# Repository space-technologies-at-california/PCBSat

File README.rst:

=============
PCB Satellite
=============
Space Technologies at Cal (https://stac.berkeley.edu)

University of California, Berkeley

Getting Started
===============
Clone this repository. Then:

Eagle
-----
#. Obtain the `STAC Eagle library <https://github.com/space-technologies-at-california/electronics>`_ by running::
   
    git submodule init
    git submodule update

#. `Add the library to Eagle <https://www.instructables.com/id/Adding-a-Library-to-Eagle-CAD/>`_.

Firmware
--------
#. Install `MSP430-GCC <http://www.ti.com/tool/msp430-gcc-opensource>`_ and
   `MSPDebug <https://dlbeer.co.nz/mspdebug/>`_.

#. In *firmware/*, make a new file called *msp430.mk.inc* and specify the path
   to your MSP430-GCC installation. For example::

    MSP430_TOOLCHAIN=/usr/local/gcc-msp430-ti-toolchain-5.01.02.00

#. Run ``make`` from *firmware/* to build all firmware configurations. To
   build a specific configuration, change to the appropriate subdirectory (for
   example, *debug/*) and run ``make``. If ``make`` complains about a missing
   *gitrev.h*, type ``make gitrev.h`` and re-run.

#. To change a build configuration, edit *config.h* in the appropriate
   subdirectory.

Programming
~~~~~~~~~~~
#. Obtain a programmer. We use the MSP430F5529 LaunchPad to program our sprite
   using Spy-Bi-Wire (SBW), but any SBW-compatible programmer should work.

#. Disconnect the 5V, 3V, GND, SBW RST and TST jumpers from the LaunchPad.

#. Connect the 3V, GND, SBW RST and TST jumpers on the ezFET-lite side to the
   target.

#. Run ``make prog`` to program, and run ``make verify`` to read back what was
   programmed.

Simulation
----------
Dependencies: igrf12 (https://github.com/scivision/igrf12)

#. Run ``python3 pull_iss_locdata.py``. This will collect (timestamp, latitude,longitude) data of the ISS for 9 hours at 10 second increments. This will create an output file in the current directory titled ``iss_loc_data_{timestamp}.csv``.  
#. Run ``python3 data_gen.py -f iss_loc_data_{timestamp}.csv`` where timestamp corresponds to the file created in the previous step. This will create an output file in the current directory that contains magnetometer data (x,y,z), gyrometer data (x,y,z), and the expected axis and power that the PCBSat should rotate along in addition to the file's previous contents. This output file will be titled ``full_{timestamp}.csv``. The units for the magnetometer data are Gauss and the units for the gyrometer data are radians/second.  

The models for predicting power and axis are still in progress. 

To run tensorboard, navigate to /simulations/python/ and execute `tensorboard --logdir="tmp/model/"`. Make sure that you have the most recent versions of tensorflow and tensorboard installed. 

Directory Structure
===================
- ./eagle : Contains all necessary Eagle files for the sprite board

  - ./eagle/sprite-test: Contains the version of the sprite manufacture by 
    Bay Area Circuits as a test board. It is largely based on the sprite
    verison created by Zac Manchester here: https://github.com/kicksat/sprite

  - ./eagle/final-sprite: Contains the version of the sprite we are currently
    working on. Our sprite began from the attitude-sprite designed by Zac
    Mancherster here: https://github.com/kicksat/attitude-sprite

  - ./eagle/electronics: STAC Eagle library submodule. See Eagle_. Please add
    any parts to the stac.lbr file contained there.
    
- ./simulation : Contains all the simulation netlists and other data 

- ./firmware : Contains all the firmware for the sprite

- ./gerbers : Contains the gerbers for the sprites. 

`Getting Started with Sprite Development Kit <https://github.com/kicksat/sprite/wiki/Getting-started-with-the-Sprite-Development-Kit>`_

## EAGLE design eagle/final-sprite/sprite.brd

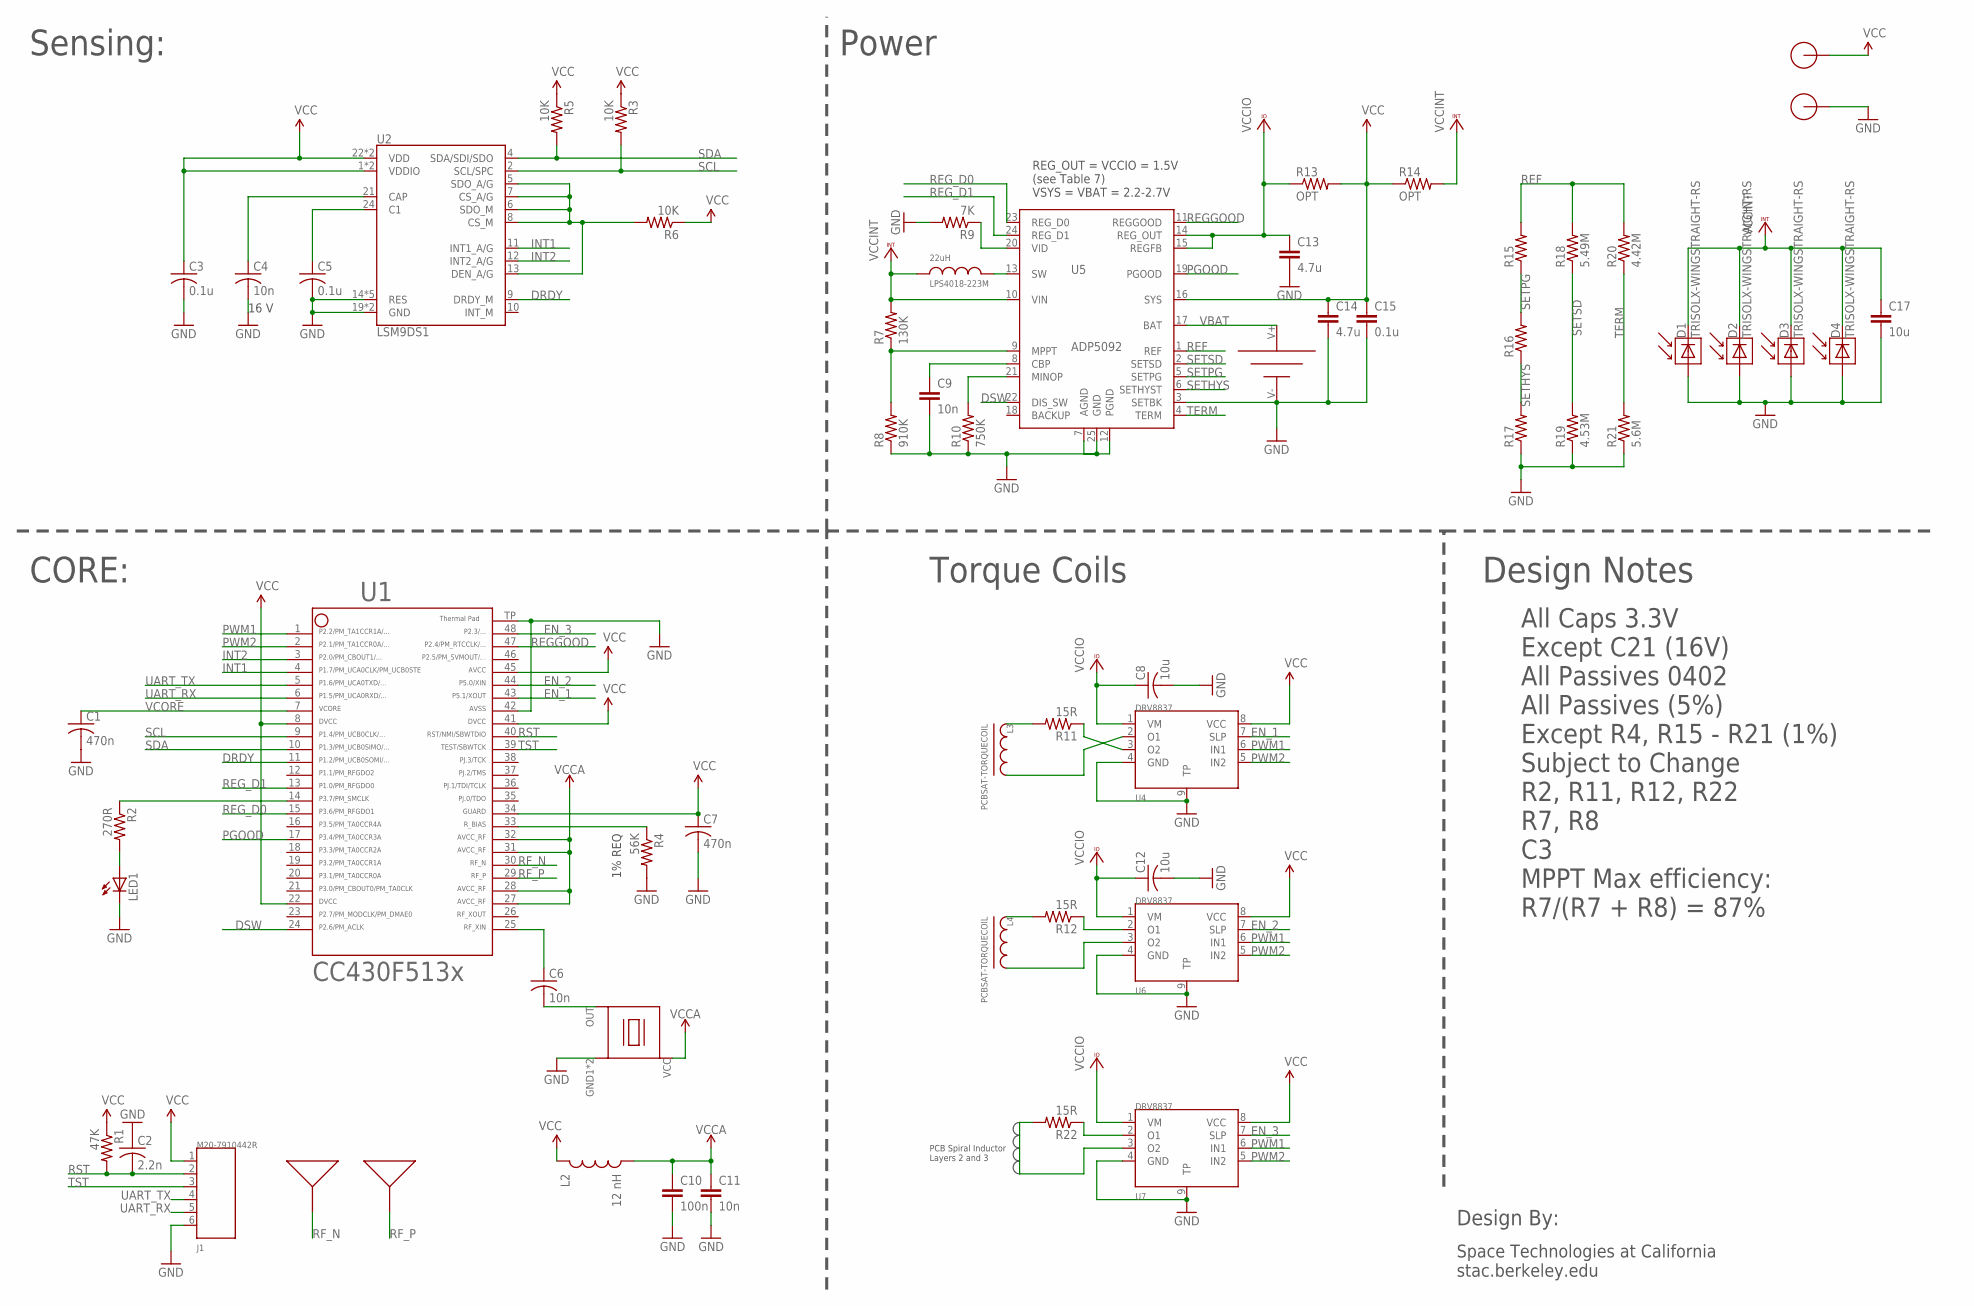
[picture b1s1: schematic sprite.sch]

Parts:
A1, A2: SPRITEANTENNA_ANTENNA
B1: UMAC_UMAC
C1, C7: 470n; C0402
C2: 2.2n; C0402
C3, C5, C15: 0.1u; C0402
C4, C6, C9, C11: 10n; C0402
C8, C12, C17: 10u; C0402
C10: 100n; C0402
C13, C14: 4.7u; C0402
D1, D2, D3, D4: TRISOLX-WINGSTRAIGHT-RS; TRISOLX-STRAIGHT-RS
J1: M20-7910442R
L1: LPS4018-223M
L2: 12 nH; 0603
L3, L4: PCBSAT-TORQUECOIL
LED1: LED0603; LED-0603
R1: 47K; R0402
R2: 270R; R0402
R3, R5, R6: 10K; R0402
R4: 56K; R0402
R7: 130K; R0402
R8: 910K; R0402
R9: 7K; R0402
R10: 750K; R0402
R11, R12, R22: 15R; R0402
R13, R14: OPT; R0402
R15, R16, R17: R-US_R0402; R0402
R18: 5.49M; R0402
R19: 4.53M; R0402
R20: 4.42M; R0402
R21: 5.6M; R0402
U1: CC430F513X; TI_MSP430_V16_RGZ48
U2: LSM9DS1; LGA24-8X4
U3: SPRITETCXO_TCXO_7Z; SPRITETCXO_TXC_7Z
U4, U6, U7: DRV8837; SON50P200X200X75-8N
U5: ADP5092; QFN50P400X400X100-25N
X1, X2: SPRITEPIN_SPRITE_PIN

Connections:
DRDY: U1.11, U2.9 (DRDY_M)
DSW: U1.24, U5.22 (DIS_SW)
EN_1: U1.43, U4.7 (SLP)
EN_2: U1.44, U6.7 (SLP)
EN_3: U1.48, U7.7 (SLP)
GND: B1.V-, C1.2, C2.1, C3.2, C4.2, C5.2, C7.2, C8.2, C9.2, C10.2, C11.2, C12.2, C13.2, C14.2, C15.2, C17.2, D1.P$1 (A), D2.P$1 (A), D3.P$1 (A), D4.P$1 (A), J1.6, LED1.C, R4.2, R8.1, R9.2, R10.1, R17.1, R19.1, R21.1, U1.42, U1.TP (49), U2.14 (RES), U2.15 (RES), U2.16 (RES), U2.17 (RES), U2.18 (RES), U2.19 (GND), U2.20 (GND), U3.GND1 (GND), U3.GND2 (GND), U4.4 (GND), U4.9 (TP), U5.3 (SETBK), U5.7 (AGND), U5.12 (PGND), U5.25 (GND), U6.4 (GND), U6.9 (TP), U7.4 (GND), U7.9 (TP), X2.PIN
INT1: U1.4, U2.11 (INT1_A/G)
INT2: U1.3, U2.12 (INT2_A/G)
unnamed: C6.1, U1.25
unnamed: R2.1, U1.14
unnamed: R4.1, U1.33
unnamed: L3.1, R11.2
unnamed: C5.1, U2.24 (C1)
unnamed: C4.1, U2.21 (CAP)
unnamed: R6.2, U2.5 (SDO_A/G), U2.6 (SDO_M), U2.7 (CS_A/G), U2.8 (CS_M), U2.13 (DEN_A/G)
unnamed: R11.1, U4.3 (O2)
unnamed: L4.1, R12.2
unnamed: LED1.A, R2.2
unnamed: C6.2, U3.OUT
unnamed: R22.1, U7.2 (O1)
unnamed: L3.2, U4.2 (O1)
unnamed: R9.1, U5.20 (VID)
unnamed: R7.1, R8.2, U5.9 (MPPT)
unnamed: R10.2, U5.21 (MINOP)
unnamed: C9.1, U5.8 (CBP)
unnamed: L1.P$2, U5.13 (SW)
unnamed: R12.1, U6.2 (O1)
unnamed: L4.2, U6.3 (O2)
unnamed: R22.2, U7.3 (O2)
PGOOD: U1.17, U5.19 (PGOOD)
PWM1: U1.1, U4.6 (IN1), U6.6 (IN1), U7.6 (IN1)
PWM2: U1.2, U4.5 (IN2), U6.5 (IN2), U7.5 (IN2)
REF: R15.2, R18.2, R20.2, U5.1 (REF)
REGGOOD: U1.47, U5.11 (REGGOOD)
REG_D0: U1.15, U5.23 (REG_D0)
REG_D1: U1.13, U5.24 (REG_D1)
RF_N: A1.IN1, A1.IN2, A1.IN3, U1.30
RF_P: A2.IN1, A2.IN2, A2.IN3, U1.29
RST: C2.2, J1.2, R1.2, U1.40
SCL: R3.2, U1.9, U2.2 (SCL/SPC)
SDA: R5.2, U1.10, U2.4 (SDA/SDI/SDO)
SETHYS: R16.1, R17.2, U5.6 (SETHYST)
SETPG: R15.1, R16.2, U5.5 (SETPG)
SETSD: R18.1, R19.2, U5.2 (SETSD)
TERM: R20.1, R21.2, U5.4 (TERM)
TST: J1.3, U1.39
UART_RX: J1.5, U1.6
UART_TX: J1.4, U1.5
VBAT: B1.V+, U5.17 (BAT)
VCC: C3.1, C7.1, C14.1, C15.1, J1.1, L2.1, R1.1, R3.1, R5.1, R6.1, R13.2, R14.1, U1.8, U1.22, U1.34, U1.41, U1.45, U2.1 (VDDIO), U2.3 (VDDIO), U2.22 (VDD), U2.23 (VDD), U4.8 (VCC), U5.16 (SYS), U6.8 (VCC), U7.8 (VCC), X1.PIN
VCCA: C10.1, C11.1, L2.2, U1.27, U1.28, U1.31, U1.32, U3.VCC
VCCINT: C17.1, D1.P$2 (C), D2.P$2 (C), D3.P$2 (C), D4.P$2 (C), L1.P$1, R7.2, R14.2, U5.10 (VIN)
VCCIO: C8.1, C12.1, C13.1, R13.1, U4.1 (VM), U5.14 (REG_OUT), U5.15 (REGFB), U6.1 (VM), U7.1 (VM)
VCORE: C1.1, U1.7

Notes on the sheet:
Sensing:
CORE:
Torque Coils
Space Technologies at California stac.berkeley.edu
Design By:
Power
REG_OUT = VCCIO = 1.5V (see Table 7) VSYS = VBAT = 2.2-2.7V
16 V
1% REQ
All Caps 3.3V Except C21 (16V) All Passives 0402 All Passives (5%) Except R4, R15 - R21 (1%) Subject to Change R2, R11, R12, R22 R7, R8 C3 MPPT Max efficiency: R7/(R7 + R8) = 87%
Design Notes
PCB Spiral Inductor Layers 2 and 3

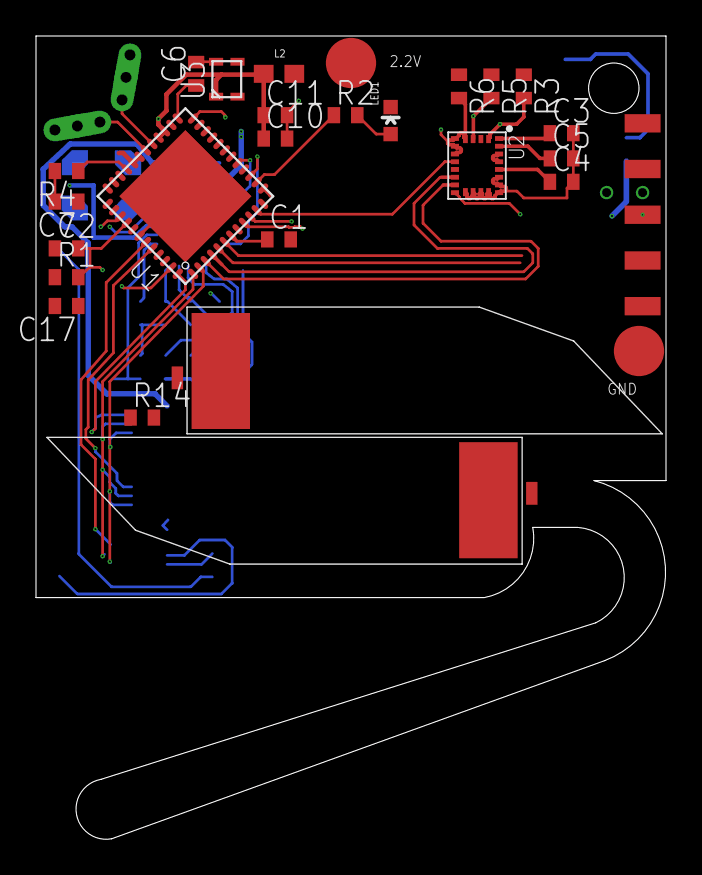
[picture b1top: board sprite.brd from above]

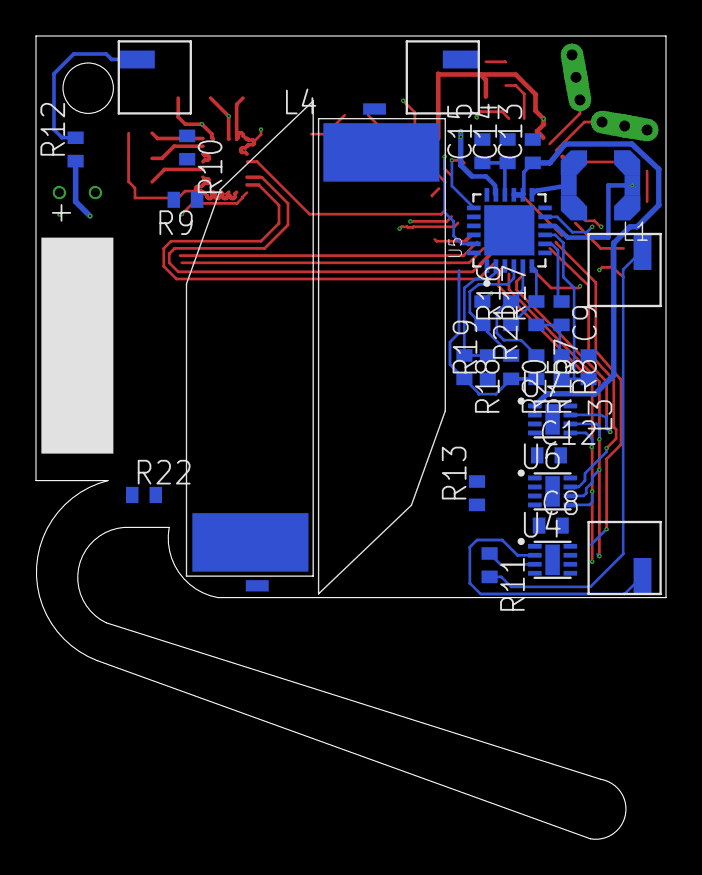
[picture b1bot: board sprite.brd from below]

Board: 4 copper layers, 35.0 x 44.6 mm, 60 parts (31 on the bottom side), 54 nets.

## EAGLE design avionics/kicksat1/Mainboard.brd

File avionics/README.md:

avionics
========

These are the EagleCAD schematics and layouts for the avionics PCBs in KickSat-2. They include a flight computer/radio (mainboard), an antenna board, and solar panels.

# License

[Creative Commons Attribution-ShareAlike 4.0 International](https://creativecommons.org/licenses/by-sa/4.0/)

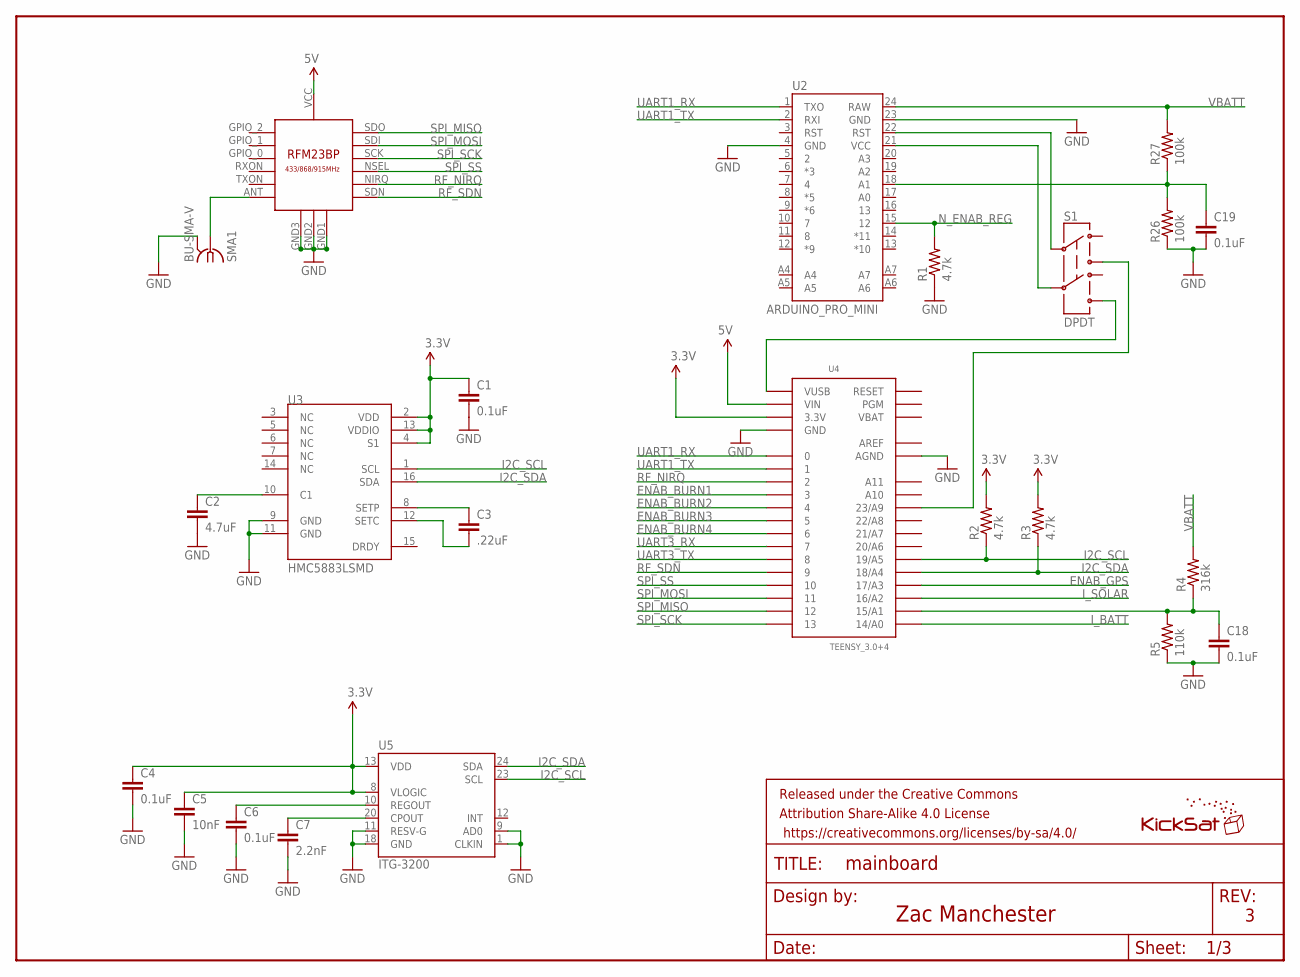
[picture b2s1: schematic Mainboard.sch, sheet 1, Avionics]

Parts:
C1, C4, C6, C18, C19: 0.1uF; 0805
C2: 4.7uF; 0805
C3: .22uF; 0805
C5: 10nF; 0805
C7: 2.2nF; 0805
FRAME1: FRAME-LETTER; CREATIVE_COMMONS
R1, R2, R3: 4.7k; 0805
R4: 316k; 0805
R5: 110k; 0805
R26, R27: 100k; 0805
S1: DPDT; AYZ0202
SMA1: BU-SMA-V
U1: RFM23BP
U2: ARDUINO_PRO_MINI
U3: HMC5883LSMD; 16LPCC
U4: TEENSY_3.0+4
U5: ITG-3200; QFN-24
U$3: KICKSAT_LOGO

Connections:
3.3V: C1.1, C4.1, C5.1, R2.2, R3.2, U3.2 (VDD), U3.4 (S1), U3.13 (VDDIO), U4.3.3V, U4.3.3V1 (3.3V), U5.8 (VLOGIC), U5.13 (VDD); also elsewhere on the board
5V: U1.VCC, U4.VIN; also elsewhere on the board
AREF: U4.AREF
ENAB_BURN1: U4.3; also elsewhere on the board
ENAB_BURN2: U4.4; also elsewhere on the board
ENAB_BURN3: U4.5; also elsewhere on the board
ENAB_BURN4: U4.6; also elsewhere on the board
ENAB_GPS: U4.17/A3; also elsewhere on the board
GND: C1.2, C2.2, C4.2, C5.2, C6.2, C7.2, C18.2, C19.2, R1.1, R5.1, R26.1, SMA1.2, SMA1.3 (2), SMA1.4 (2), SMA1.5 (2), U1.GND1, U1.GND2, U1.GND3, U2.4 (GND), U2.23 (GND), U3.9 (GND), U3.11 (GND), U4.AGND, U4.GND, U4.GND1 (GND), U5.1 (CLKIN), U5.9 (AD0), U5.11 (RESV-G), U5.18 (GND); also elsewhere on the board
I2C_SCL: R2.1, U3.1 (SCL), U4.19/A5, U5.23 (SCL)
I2C_SDA: R3.1, U3.16 (SDA), U4.18/A4, U5.24 (SDA)
I_BATT: U4.14/A0; also elsewhere on the board
I_SOLAR: U4.16/A2; also elsewhere on the board
unnamed: S1.3, U4.23/A9
unnamed: S1.6, U4.VUSB
unnamed: C19.1, R26.2, R27.1, U2.18 (A1)
unnamed: SMA1.1, U1.ANT
unnamed: C18.1, R4.1, R5.2, U4.15/A1
unnamed: C7.1, U5.20 (CPOUT)
unnamed: C6.1, U5.10 (REGOUT)
unnamed: C2.1, U3.10 (C1)
unnamed: C3.1, U3.8 (SETP)
unnamed: C3.2, U3.12 (SETC)
N_ENAB_REG: R1.2, U2.15 (12); also elsewhere on the board
PGM_RST: S1.2, U2.22 (RST)
PGM_VCC: S1.5, U2.21 (VCC)
RF_NIRQ: U1.NIRQ, U4.2
RF_SDN: U1.SDN, U4.9
SPI_MISO: U1.SDO, U4.12
SPI_MOSI: U1.SDI, U4.11
SPI_SCK: U1.SCK, U4.13
SPI_SS: U1.NSEL, U4.10
UART1_RX: U2.1 (TXO), U4.0
UART1_TX: U2.2 (RXI), U4.1
UART3_RX: U4.7; also elsewhere on the board
UART3_TX: U4.8; also elsewhere on the board
VBAT: U4.VBAT
VBATT: R4.2, R27.2, U2.24 (RAW); also elsewhere on the board

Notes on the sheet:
Zac Manchester

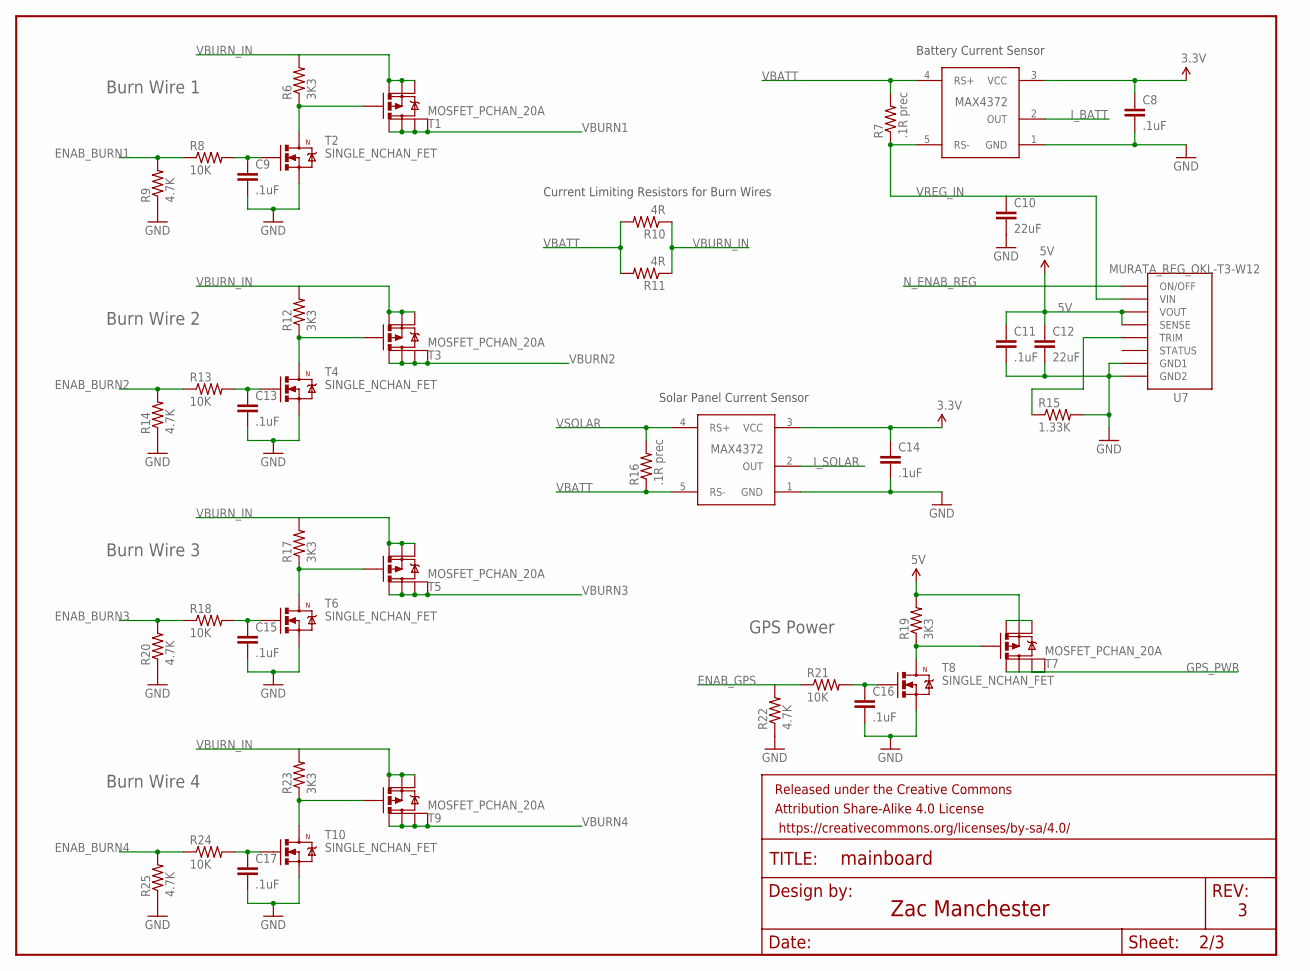
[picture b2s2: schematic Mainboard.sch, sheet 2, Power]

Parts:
C8, C9, C11, C13, C14, C15, C16, C17: .1uF; 0805
C10, C12: 22uF; 1206
FRAME2: FRAME-LETTER; CREATIVE_COMMONS
R6, R12, R17, R19, R23: 3K3; 0805
R7, R16: .1R prec; 0805
R8, R13, R18, R21, R24: 10K; 0805
R9, R14, R20, R22, R25: 4.7K; 0805
R10, R11: 4R; R2512
R15: 1.33K; 0805
T1, T3, T5, T7, T9: MOSFET_PCHAN_20A; SO8
T2, T4, T6, T8, T10: SINGLE_NCHAN_FET; SOT23-3
U6, U8: CURRENT_MAX4372; SOT23-5
U7: MURATA_REG_OKL-T3-W12; MURATA_REG_OKL-T6-W12

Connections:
3.3V: C8.1, C14.1, U6.3 (VCC), U8.3 (VCC); also elsewhere on the board
5V: C11.1, C12.1, R19.2, T7.1 (S), T7.2 (S), T7.3 (S), U7.4 (VOUT), U7.5 (SENSE); also elsewhere on the board
ENAB_BURN1: R8.1, R9.2; also elsewhere on the board
ENAB_BURN2: R13.1, R14.2; also elsewhere on the board
ENAB_BURN3: R18.1, R20.2; also elsewhere on the board
ENAB_BURN4: R24.1, R25.2; also elsewhere on the board
ENAB_GPS: R21.1, R22.2; also elsewhere on the board
GND: C8.2, C9.2, C10.2, C11.2, C12.2, C13.2, C14.2, C15.2, C16.2, C17.2, R9.1, R14.1, R15.2, R20.1, R22.1, R25.1, T2.2 (S), T4.2 (S), T6.2 (S), T8.2 (S), T10.2 (S), U6.1 (GND), U7.3 (GND1), U7.7 (GND2), U8.1 (GND); also elsewhere on the board
GPS_PWR: T7.5 (D), T7.6 (D), T7.7 (D), T7.8 (D); also elsewhere on the board
I_BATT: U6.2 (OUT); also elsewhere on the board
I_SOLAR: U8.2 (OUT); also elsewhere on the board
unnamed: C13.1, R13.2, T4.1 (G)
unnamed: R12.1, T3.4 (G), T4.3 (D)
unnamed: C15.1, R18.2, T6.1 (G)
unnamed: R17.1, T5.4 (G), T6.3 (D)
unnamed: R15.1, U7.6 (TRIM)
unnamed: C17.1, R24.2, T10.1 (G)
unnamed: R23.1, T9.4 (G), T10.3 (D)
unnamed: C16.1, R21.2, T8.1 (G)
unnamed: R19.1, T7.4 (G), T8.3 (D)
unnamed: C9.1, R8.2, T2.1 (G)
unnamed: R6.1, T1.4 (G), T2.3 (D)
N_ENAB_REG: U7.1 (ON/OFF); also elsewhere on the board
VBATT: R7.2, R10.2, R11.2, R16.1, U6.4 (RS+), U8.5 (RS-); also elsewhere on the board
VBURN1: T1.5 (D), T1.6 (D), T1.7 (D), T1.8 (D); also elsewhere on the board
VBURN2: T3.5 (D), T3.6 (D), T3.7 (D), T3.8 (D); also elsewhere on the board
VBURN3: T5.5 (D), T5.6 (D), T5.7 (D), T5.8 (D); also elsewhere on the board
VBURN4: T9.5 (D), T9.6 (D), T9.7 (D), T9.8 (D); also elsewhere on the board
VBURN_IN: R6.2, R10.1, R11.1, R12.2, R17.2, R23.2, T1.1 (S), T1.2 (S), T1.3 (S), T3.1 (S), T3.2 (S), T3.3 (S), T5.1 (S), T5.2 (S), T5.3 (S), T9.1 (S), T9.2 (S), T9.3 (S)
VREG_IN: C10.1, R7.1, U6.5 (RS-), U7.2 (VIN)
VSOLAR: R16.2, U8.4 (RS+); also elsewhere on the board

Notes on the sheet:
Burn Wire 1
Burn Wire 2
Burn Wire 3
Solar Panel Current Sensor
Battery Current Sensor
Burn Wire 4
Current Limiting Resistors for Burn Wires
Zac Manchester
GPS Power

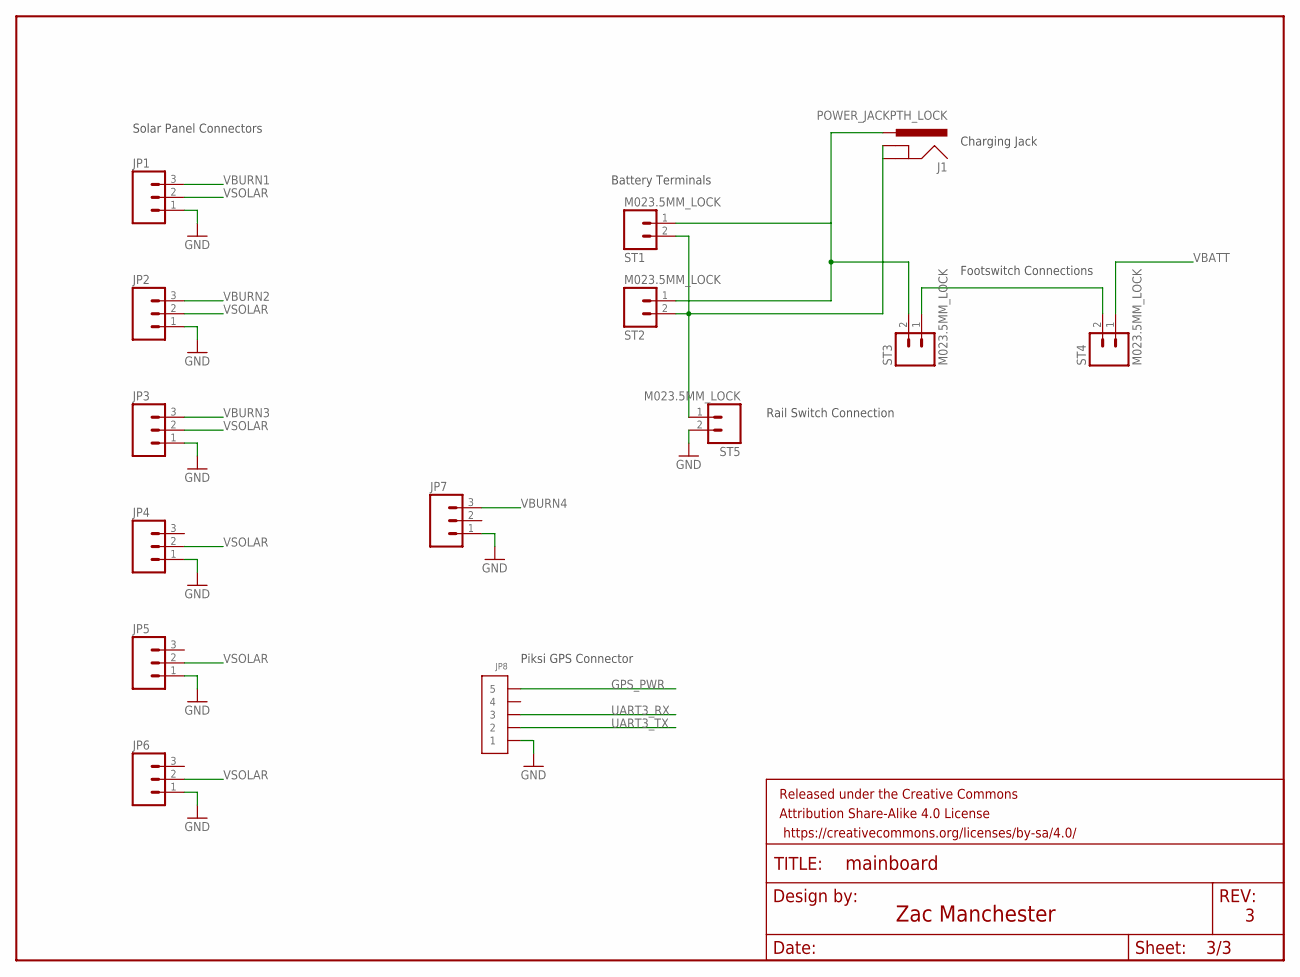
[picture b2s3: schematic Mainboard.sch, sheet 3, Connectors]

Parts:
FRAME3: FRAME-LETTER; CREATIVE_COMMONS
J1: POWER_JACKPTH_LOCK; POWER_JACK_PTH_LOCK
JP1, JP2, JP3, JP4, JP5, JP6, JP7: M03POLAR_LOCK; MOLEX-1X3_LOCK
JP8: CONN_5-1-53261; PB-53261-05
ST1, ST2, ST3, ST4, ST5: M023.5MM_LOCK; SCREWTERMINAL-3.5MM-2_LOCK

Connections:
BATT_INPUT: J1.PWR, ST1.1, ST2.1, ST3.2
GND: JP1.1, JP2.1, JP3.1, JP4.1, JP5.1, JP6.1, JP7.1, JP8.1, ST5.2; also elsewhere on the board
GPS_PWR: JP8.5; also elsewhere on the board
unnamed: J1.GND, J1.GNDBREAK, ST1.2, ST2.2, ST5.1
unnamed: ST3.1, ST4.2
UART3_RX: JP8.3; also elsewhere on the board
UART3_TX: JP8.2; also elsewhere on the board
VBATT: ST4.1; also elsewhere on the board
VBURN1: JP1.3; also elsewhere on the board
VBURN2: JP2.3; also elsewhere on the board
VBURN3: JP3.3; also elsewhere on the board
VBURN4: JP7.3; also elsewhere on the board
VSOLAR: JP1.2, JP2.2, JP3.2, JP4.2, JP5.2, JP6.2; also elsewhere on the board

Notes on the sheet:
Footswitch Connections
Solar Panel Connectors
Battery Terminals
Rail Switch Connection
Charging Jack
Piksi GPS Connector
Zac Manchester

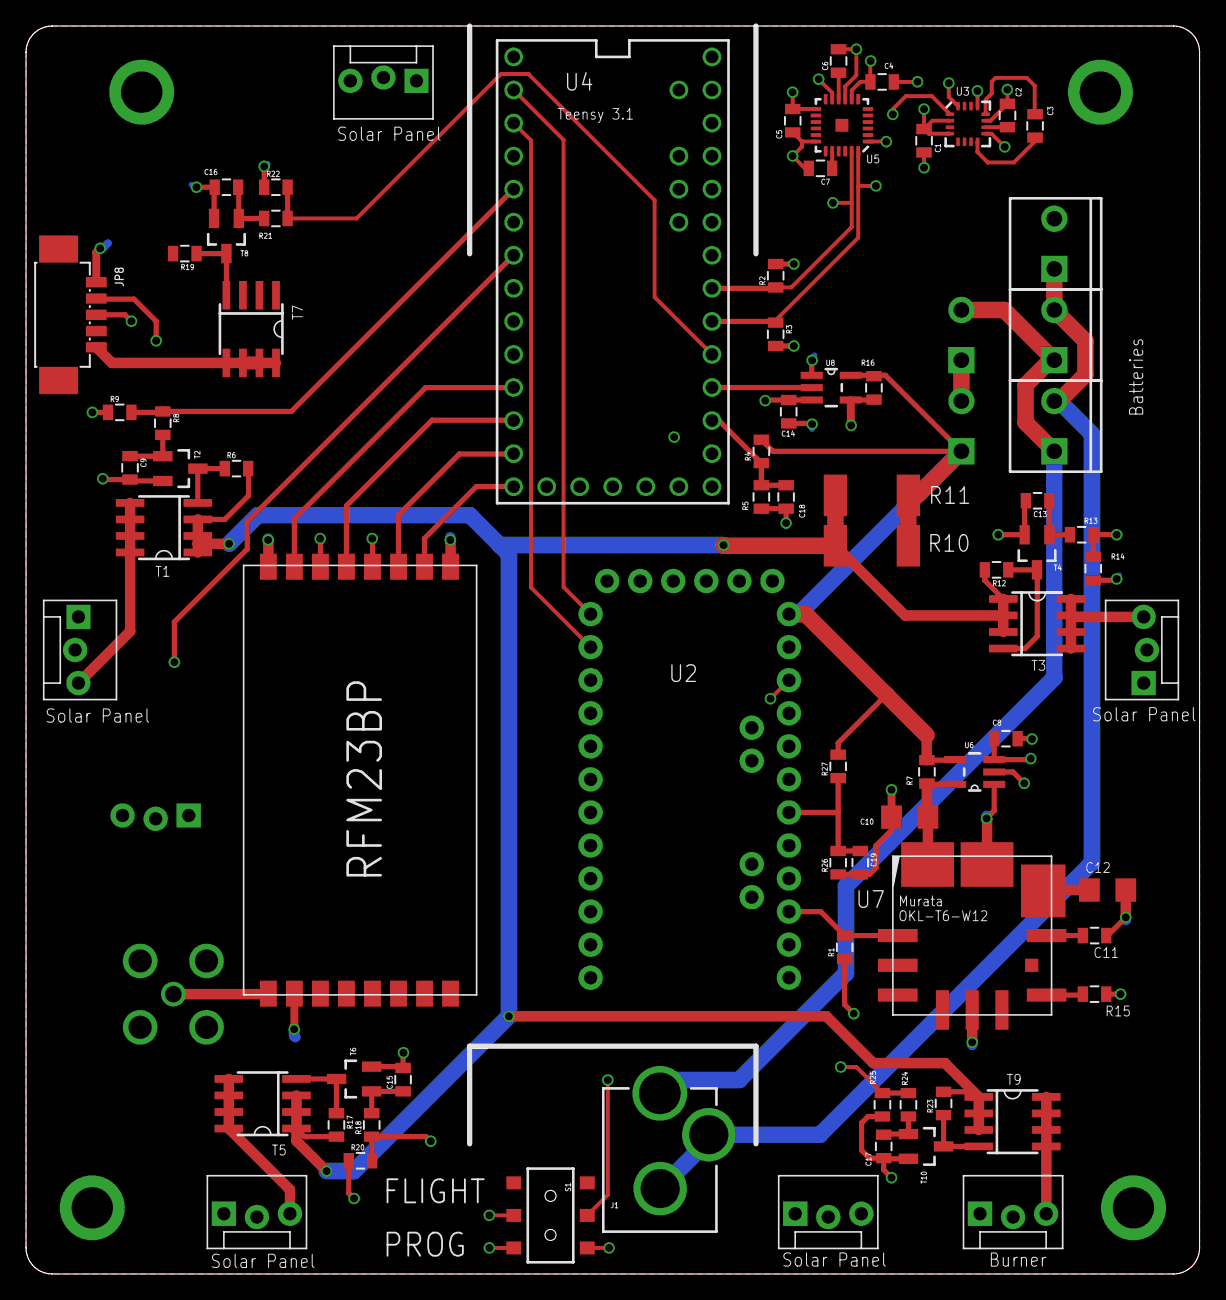
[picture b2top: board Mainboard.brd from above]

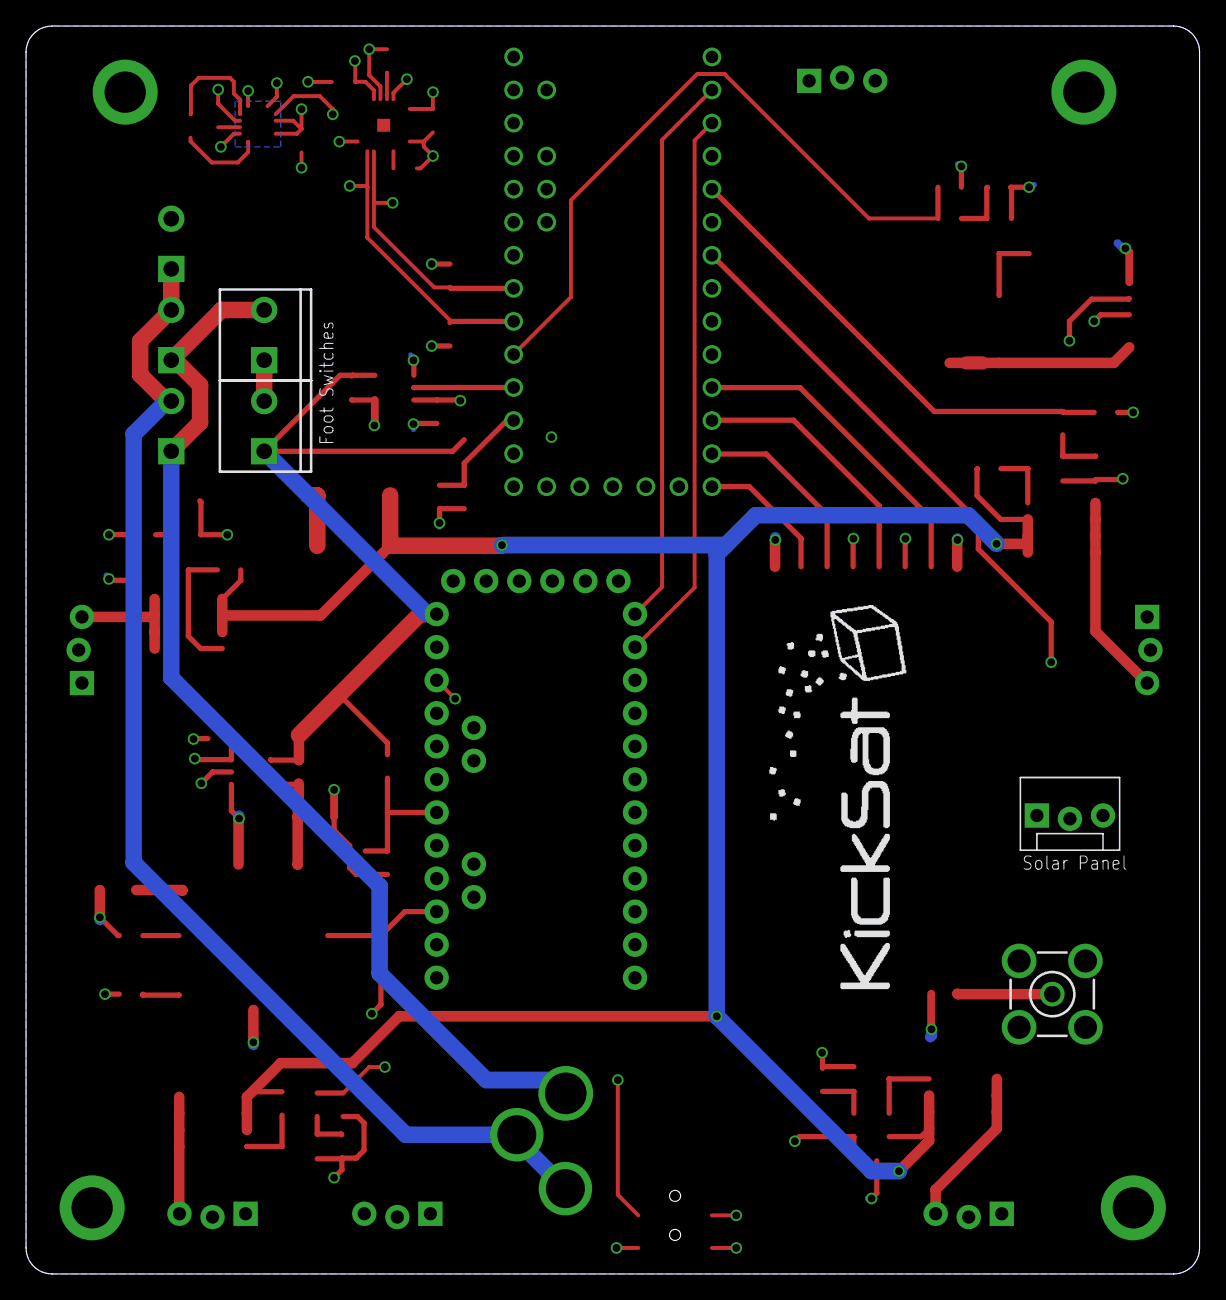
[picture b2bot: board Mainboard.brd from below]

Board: 4 copper layers, 90.2 x 95.9 mm, 84 parts (5 on the bottom side), 58 nets.

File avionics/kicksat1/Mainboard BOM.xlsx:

Qty | Value | Device | Package | Parts | Description
3 | 4.7k | Resistor | 0805 | R1, R2, R3 | Resistor
1 | 120k | Resistor | 0805 | R4 | Resistor
1 | 68k | Resistor | 0805 | R5 | Resistor
5 | 3K3 | Resistor | 0805 | R6, R12, R17, R19, R23 | Resistor
2 | .1R prec | Resistor | 0805 | R7, R16 | Resistor
5 | 10K | Resistor | 0805 | R8, R13, R18, R21, R24 | Resistor
5 | 4.7K | Resistor | 0805 | R9, R14, R20, R22, R25 | Resistor
2 | 4.7R | Resistor | 2512 | R10, R11 | Resistor
1 | 1.33K | Resistor | 0805 | R15 | Resistor
3 | 0.1uF | Capacitor | 0805 | C1, C4, C6 | Capacitor
1 | 4.7uF | Capacitor | 0805 | C2 | Capacitor
1 | .22uF | Capacitor | 0805 | C3 | Capacitor
1 | 10nF | Capacitor | 0805 | C5 | Capacitor
1 | 2.2nF | Capacitor | 0805 | C7 | Capacitor
8 | .1uF | Capacitor | 0805 | C8, C9, C11, C13, C14, C15, C16, C17 | Capacitor
2 | 22uF | Capacitor | 1206 | C10, C12 | Capacitor
5 | MOSFET_PCHAN_20A | MOSFET_PCHAN_20A | SO8 | T1, T3, T5, T7, T9 | Power MOSFET for Burn Wires
5 | SINGLE_NCHAN_FET | SINGLE_NCHAN_FET | SOT23-3 | T2, T4, T6, T8, T10 | MOSFET for burn wire circuit
1 | RFM23BP | RFM23BP | RFM23BP | U1 | HopeRF RFM23BP Radio
1 | ARDUINO_PRO_MINI | ARDUINO_PRO_MINI | ARDUINO_PRO_MINI | U2 | Watchdog MCU
1 | HMC5883LSMD | HMC5883LSMD | 16LPCC | U3 | 3 Axis Digital Compass IC
1 | TEENSY_3.0+4 | TEENSY_3.0+4 | TEENSY_3.0+4 | U4 | Flight computer MCU
1 | ITG-3200 | ITG-3200 | QFN-24 | U5 | ITG-3200 3-axis gyro, digital output, qfn24 package
2 | CURRENT_MAX4372 | CURRENT_MAX4372 | SOT23-5 | U6, U8 | Current Sense Amplifier
1 | MURATA_REG_OKL-T3-W12 | MURATA_REG_OKL-T6-W12 | MURATA_REG_OKL-T6-W12 | U7 | Switching Regulator
5 | M023.5MM_LOCK | M023.5MM_LOCK | SCREWTERMINAL-3.5MM-2_LOCK | ST1, ST2, ST3, ST4, ST5 | Screw terminals for battery + foot switch connections
1 | BU-SMA-V | BU-SMA-V | BU-SMA-V | SMA1 | Antenna connector (MCX)
1 | CONN_5-1-53261 | CONN_5-1-53261 | PB-53261-05 | JP8 | Piksi GPS connector
7 | M03POLAR_LOCK | M03POLAR_LOCK | MOLEX-1X3_LOCK | JP1, JP2, JP3, JP4, JP5, JP6, JP7 | Solar Panel Connectors
1 | POWER_JACKPTH_LOCK | POWER_JACKPTH_LOCK | POWER_JACK_PTH_LOCK | J1 | Charging Jack
1 | DPDT | SWITCH-DPDTAYZ0202 | AYZ0202 | S1 | Switch for MCU programming mode

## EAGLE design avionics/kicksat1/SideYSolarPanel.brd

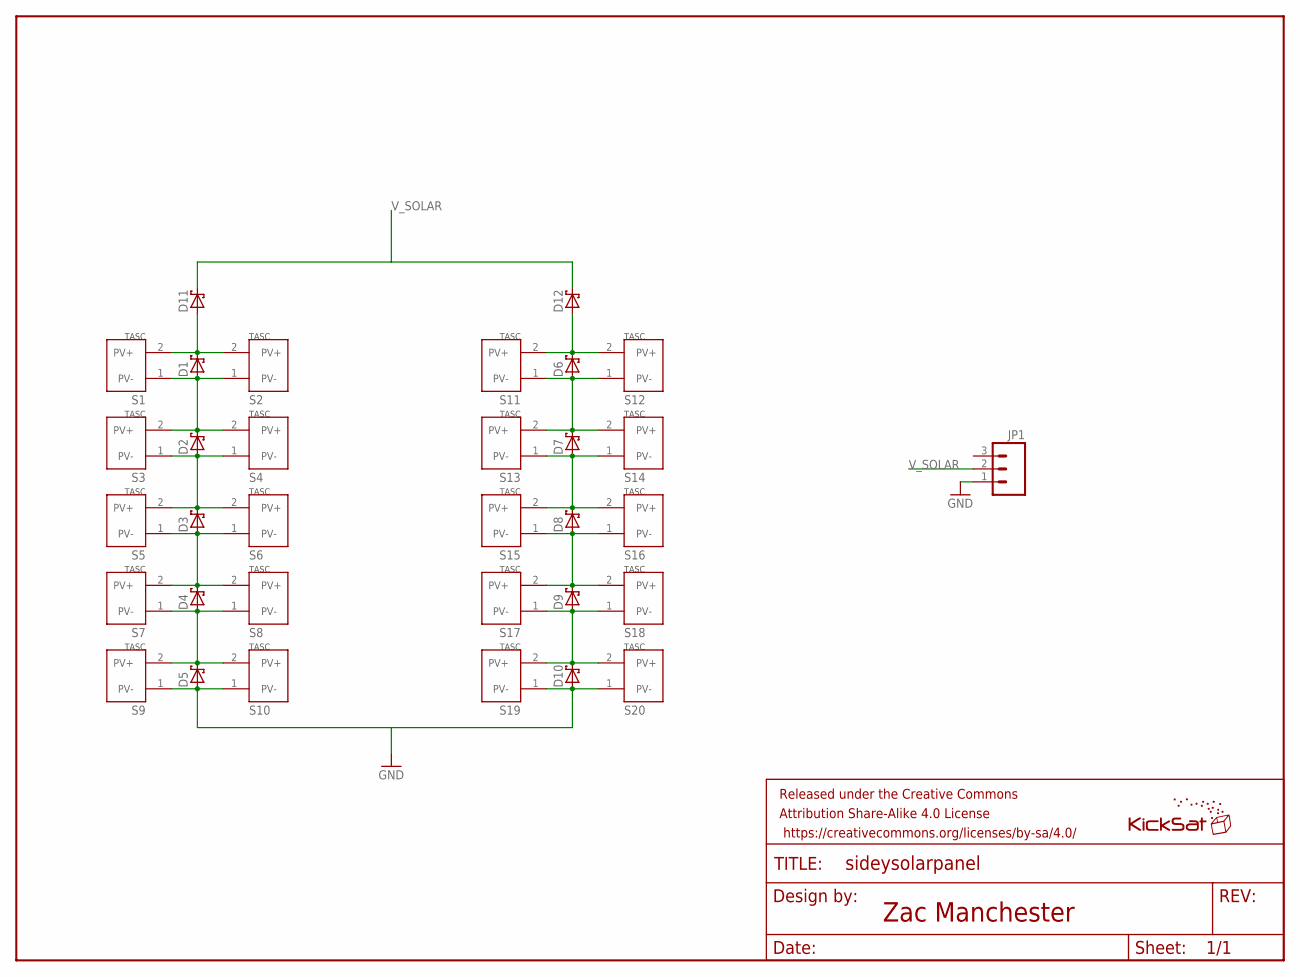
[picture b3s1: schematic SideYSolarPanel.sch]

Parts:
D1, D2, D3, D4, D5, D6, D7, D8, D9, D10, D11, D12: SB_DIODE
FRAME1: FRAME-LETTER; CREATIVE_COMMONS
JP1: M03POLAR_LOCK; MOLEX-1X3_LOCK
S1, S2, S3, S4, S5, S6, S7, S8, S9, S10, S11, S12, S13, S14, S15, S16, S17, S18, S19, S20: SOLAR_CELL
U$1: KICKSAT_LOGO

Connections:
GND: D5.POS, D10.POS, JP1.1, S9.1 (PV-), S10.1 (PV-), S19.1 (PV-), S20.1 (PV-)
unnamed: D6.POS, D7.NEG, S11.1 (PV-), S12.1 (PV-), S13.2 (PV+), S14.2 (PV+)
unnamed: D6.NEG, D12.POS, S11.2 (PV+), S12.2 (PV+)
unnamed: D7.POS, D8.NEG, S13.1 (PV-), S14.1 (PV-), S15.2 (PV+), S16.2 (PV+)
unnamed: D1.NEG, D11.POS, S1.2 (PV+), S2.2 (PV+)
unnamed: D8.POS, D9.NEG, S15.1 (PV-), S16.1 (PV-), S17.2 (PV+), S18.2 (PV+)
unnamed: D2.POS, D3.NEG, S3.1 (PV-), S4.1 (PV-), S5.2 (PV+), S6.2 (PV+)
unnamed: D3.POS, D4.NEG, S5.1 (PV-), S6.1 (PV-), S7.2 (PV+), S8.2 (PV+)
unnamed: D9.POS, D10.NEG, S17.1 (PV-), S18.1 (PV-), S19.2 (PV+), S20.2 (PV+)
unnamed: D1.POS, D2.NEG, S1.1 (PV-), S2.1 (PV-), S3.2 (PV+), S4.2 (PV+)
unnamed: D4.POS, D5.NEG, S7.1 (PV-), S8.1 (PV-), S9.2 (PV+), S10.2 (PV+)
V_SOLAR: D11.NEG, D12.NEG, JP1.2

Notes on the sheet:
Zac Manchester

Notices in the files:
tools/energia/Sprite_7/pins_energia.h:
Copyright (c) 2012 Robert Wessels. All right reserved.
Copyright (c) 2007 David A. Mellis
Public License along with this library; if not, write to the
Free Software Foundation, Inc., 59 Temple Place, Suite 330,
Boston, MA  02111-1307  USA
parts and their libraries:
SparkFun-Capacitors: Licensing: Creative Commons ShareAlike 4.0 International - https://creativecommons.org/licenses/by-sa/4.0
SparkFun-Aesthetics: Released under the Creative Commons Attribution Share-Alike 4.0 License
SparkFun-Aesthetics: Released under the Creative Commons
